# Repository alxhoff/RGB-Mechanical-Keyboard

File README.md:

# RGB-Mechanical-Keyboard

In this repository you will find my PCBs for a mechanical keyboard based around cherry switches and WS2812 single-wire serial RGB LEDs.
The keyboard is broken into two parts, the main keyboard PCB that houses the LEDS, power supply and switches, and a daughterboard that connects via ribbon cable where the controlling microcontroller is mounter.

The keyboard PCB in the latest generation has been been built such that the bottom row can be arranged in many different ways, allowing for unique configuration.
On the to-do list is to add this sort of customizability to more of the keyboard, eg. replacing capslock (totally useless) with a couple of macro keys.

# TODO for V2.1

- [x] Make second-from-bottom row more customizable
- [x] Add a usb 2.0 hub and a couple of usb-c ports to the keyboard.
- [X] Add jumpers to configure rgb rows, for example, daisy chaining multiple rows to reduce required pin count
- [ ] STM32F411 "Blackpill" control board
- [X] Add port for connecting a joystick for mouse functionality
- [X] Add switch for toggling 'BOOT' protocol, ie. device can recognize that it should send 8 byte BOOT compatible HID reports
- [X] Update existing control boards to handle 30 pin ribbon cable
- [X] Add hotswappable sockets
- [X] Make mounting holes elongated to allow for less precision during case fabrication

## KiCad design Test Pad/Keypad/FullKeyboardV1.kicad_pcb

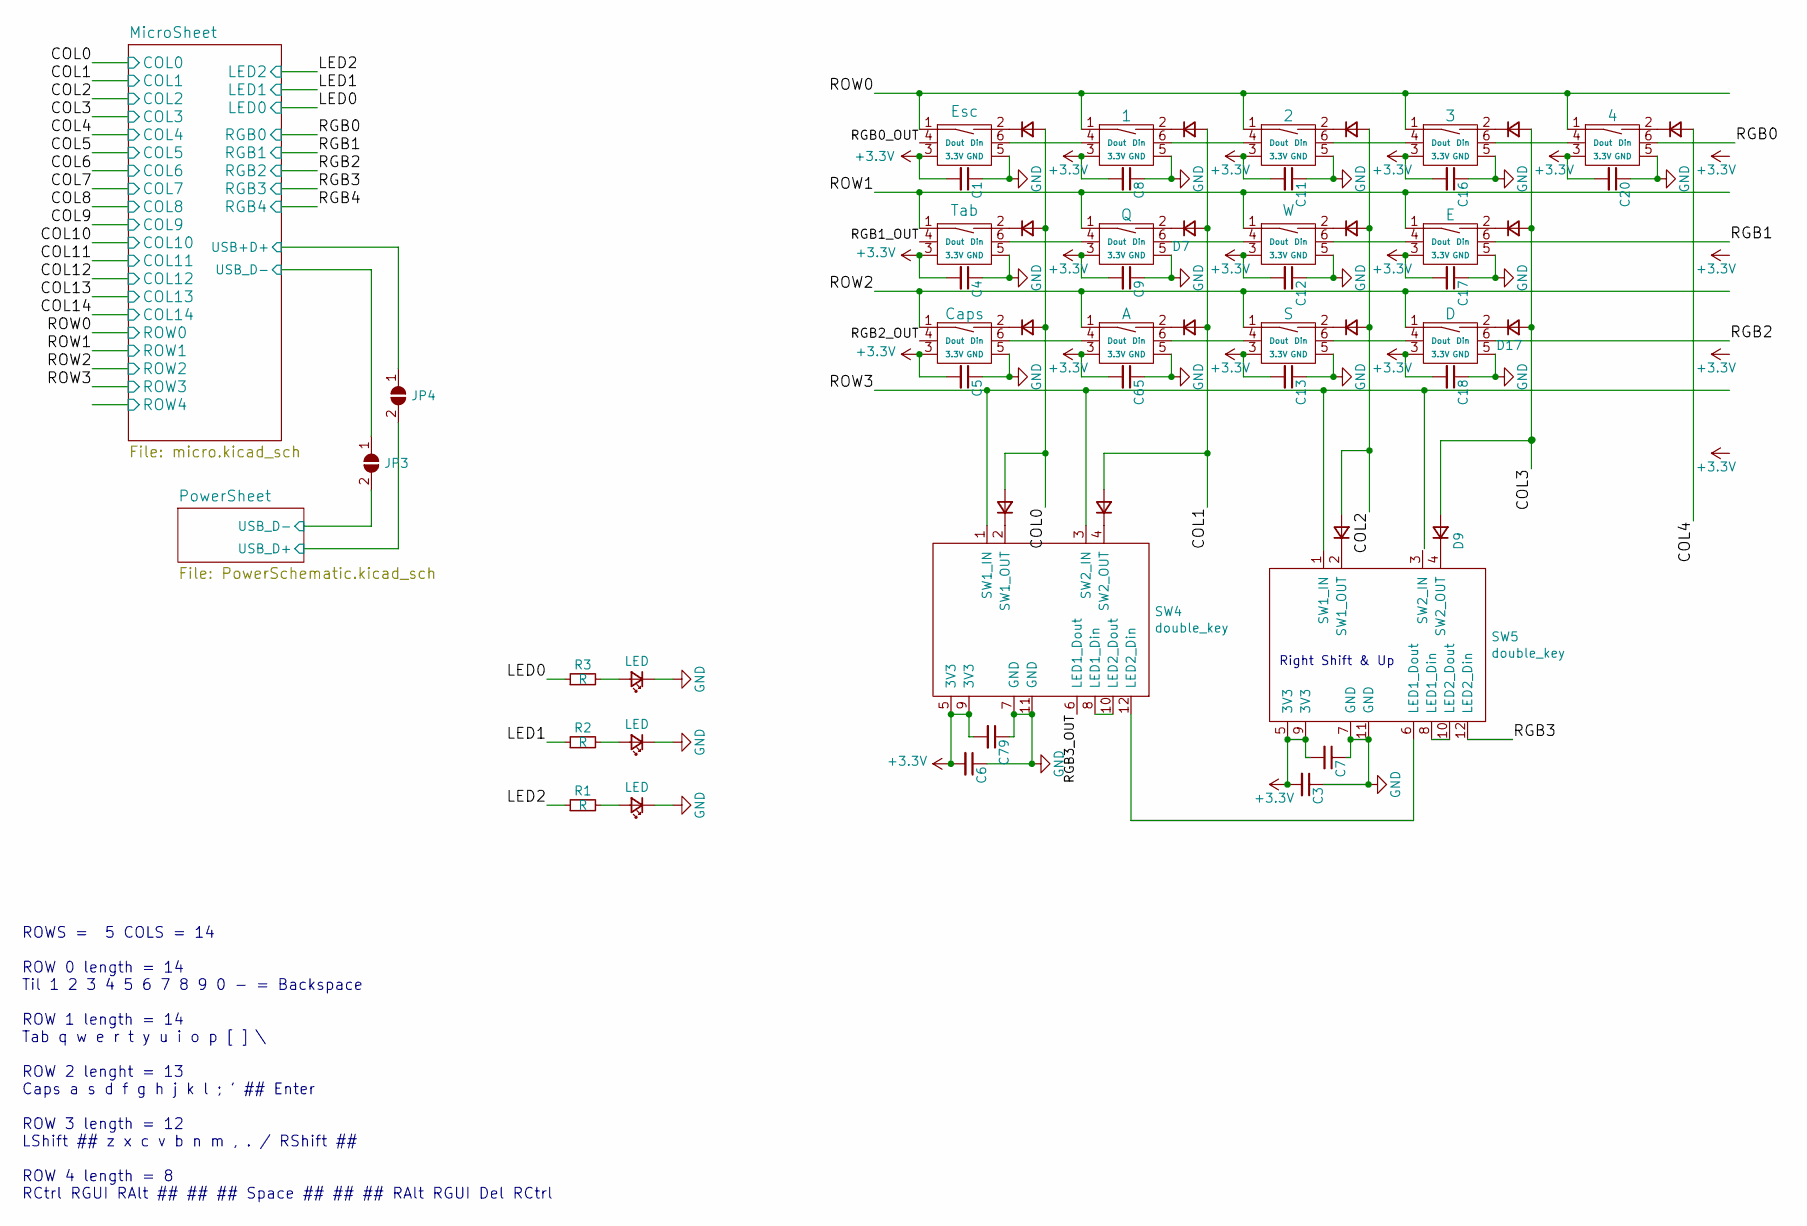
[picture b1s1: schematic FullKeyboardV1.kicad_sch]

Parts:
C1, C3, C4, C5, C6, C7, C8, C9, C11, C12, C13, C16, C17, C18, C20, C65, C79: C_Small; C_0603_1608Metric
D1, D2, D3, D4, D5, D6, D7, D8, D9, D10, D11, D12, D15, D16, D17, D19, D77: D_Small; D_SOD-123
D70, D71, D72: LED; LED_0603_1608Metric
JP3, JP4: SolderJumper_2_Open; SolderJumper-2_P1.3mm_Open_RoundedPad1.0x1.5mm
R1, R2, R3: R; R_0603_1608Metric
SW1: Esc; RGB_CHERRY_PCB_100H_HOTSWAP
SW2: Tab; RGB_CHERRY_PCB_150H_HOTSWAP
SW3: Caps; RGB_CHERRY_PCB_175H_HOTSWAP
SW4: double_key; RGB_CHERRY_SHIFT_ROW_LEFT
SW5: double_key; RGB_CHERRY_SHIFT_RIGHT_2.0
SW6: 1; RGB_CHERRY_PCB_100H_HOTSWAP
SW7: Q; RGB_CHERRY_PCB_100H_HOTSWAP
SW8: A; RGB_CHERRY_PCB_100H_HOTSWAP
SW10: 2; RGB_CHERRY_PCB_100H_HOTSWAP
SW11: W; RGB_CHERRY_PCB_100H_HOTSWAP
SW12: S; RGB_CHERRY_PCB_100H_HOTSWAP
SW15: 3; RGB_CHERRY_PCB_100H_HOTSWAP
SW16: E; RGB_CHERRY_PCB_100H_HOTSWAP
SW17: D; RGB_CHERRY_PCB_100H_HOTSWAP
SW19: 4; RGB_CHERRY_PCB_100H_HOTSWAP

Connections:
/COL0: D1.2 (A), D2.2 (A), D3.2 (A), D4.2 (A); also elsewhere on the board
/COL1: D6.2 (A), D7.2 (A), D8.2 (A), D77.2 (A); also elsewhere on the board
/COL2: D5.2 (A), D10.2 (A), D11.2 (A), D12.2 (A); also elsewhere on the board
/COL3: D9.2 (A), D15.2 (A), D16.2 (A), D17.2 (A); also elsewhere on the board
/COL4: D19.2 (A); also elsewhere on the board
/LED0: R3.1; also elsewhere on the board
/LED1: R2.1; also elsewhere on the board
/LED2: R1.1; also elsewhere on the board
/MicroSheet/USB+D+: JP4.1 (A); also elsewhere on the board
/MicroSheet/USB_D-: JP3.1 (A); also elsewhere on the board
/PowerSheet/USB_D+: JP4.2 (B); also elsewhere on the board
/PowerSheet/USB_D-: JP3.2 (B); also elsewhere on the board
/RGB0: SW19.6 (Din); also elsewhere on the board
/RGB0_OUT: SW1.4 (Dout)
/RGB1: SW16.6 (Din); also elsewhere on the board
/RGB1_OUT: SW2.4 (Dout)
/RGB2: SW17.6 (Din); also elsewhere on the board
/RGB2_OUT: SW3.4 (Dout)
/RGB3: SW5.12 (LED2_Din); also elsewhere on the board
/RGB3_OUT: SW4.6 (LED1_Dout)
/ROW0: SW1.1, SW6.1, SW10.1, SW15.1, SW19.1; also elsewhere on the board
/ROW1: SW2.1, SW7.1, SW11.1, SW16.1; also elsewhere on the board
/ROW2: SW3.1, SW8.1, SW12.1, SW17.1; also elsewhere on the board
/ROW3: SW4.1 (SW1_IN), SW4.3 (SW2_IN), SW5.1 (SW1_IN); also elsewhere on the board
GND: C1.1, C3.1, C4.1, C5.1, C6.1, C7.1, C8.1, C9.1, C11.1, C12.1, C13.1, C16.1, C17.1, C18.1, C20.1, C65.1, C79.1, D70.1 (K), D71.1 (K), D72.1 (K), SW1.5 (GND), SW2.5 (GND), SW3.5 (GND), SW4.7 (GND), SW4.11 (GND), SW5.7 (GND), SW5.11 (GND), SW6.5 (GND), SW7.5 (GND), SW8.5 (GND), SW10.5 (GND), SW11.5 (GND), SW12.5 (GND), SW15.5 (GND), SW16.5 (GND), SW17.5 (GND), SW19.5 (GND); also elsewhere on the board
unnamed: D1.1 (K), SW1.2
unnamed: D2.1 (K), SW2.2
unnamed: D3.1 (K), SW3.2
unnamed: D4.1 (K), SW4.2 (SW1_OUT)
unnamed: D5.1 (K), SW5.2 (SW1_OUT)
unnamed: D6.1 (K), SW6.2
unnamed: D7.1 (K), SW7.2
unnamed: D8.1 (K), SW8.2
unnamed: D9.1 (K), SW5.4 (SW2_OUT)
unnamed: D10.1 (K), SW10.2
unnamed: D11.1 (K), SW11.2
unnamed: D12.1 (K), SW12.2
unnamed: D15.1 (K), SW15.2
unnamed: D16.1 (K), SW16.2
unnamed: D17.1 (K), SW17.2
unnamed: D19.1 (K), SW19.2
unnamed: D70.2 (A), R1.2
unnamed: D71.2 (A), R2.2
unnamed: D72.2 (A), R3.2
unnamed: D77.1 (K), SW4.4 (SW2_OUT)
unnamed: SW1.6 (Din), SW6.4 (Dout)
unnamed: SW2.6 (Din), SW7.4 (Dout)
unnamed: SW3.6 (Din), SW8.4 (Dout)
unnamed: SW4.8 (LED1_Din), SW4.10 (LED2_Dout)
unnamed: SW4.12 (LED2_Din), SW5.6 (LED1_Dout)
unnamed: SW5.8 (LED1_Din), SW5.10 (LED2_Dout)
unnamed: SW6.6 (Din), SW10.4 (Dout)
unnamed: SW10.6 (Din), SW15.4 (Dout)
unnamed: SW7.6 (Din), SW11.4 (Dout)
unnamed: SW11.6 (Din), SW16.4 (Dout)
unnamed: SW8.6 (Din), SW12.4 (Dout)
unnamed: SW12.6 (Din), SW17.4 (Dout)
unnamed: SW15.6 (Din), SW19.4 (Dout)

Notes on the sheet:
Right Shift & Up
ROWS = 5 COLS = 14 ROW 0 length = 14 Til 1 2 3 4 5 6 7 8 9 0 - = Backspace ROW 1 length = 14 Tab q w e r t y u i o p [ ] \ ROW 2 lenght = 13 Caps a s d f g h j k l ; ' ## Enter ROW 3 length = 12 LShift ## z x c v b n m , . / RShift ## ROW 4 length = 8 RCtrl RGUI RAlt ## ## ## Space ## ## ## RAlt RG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

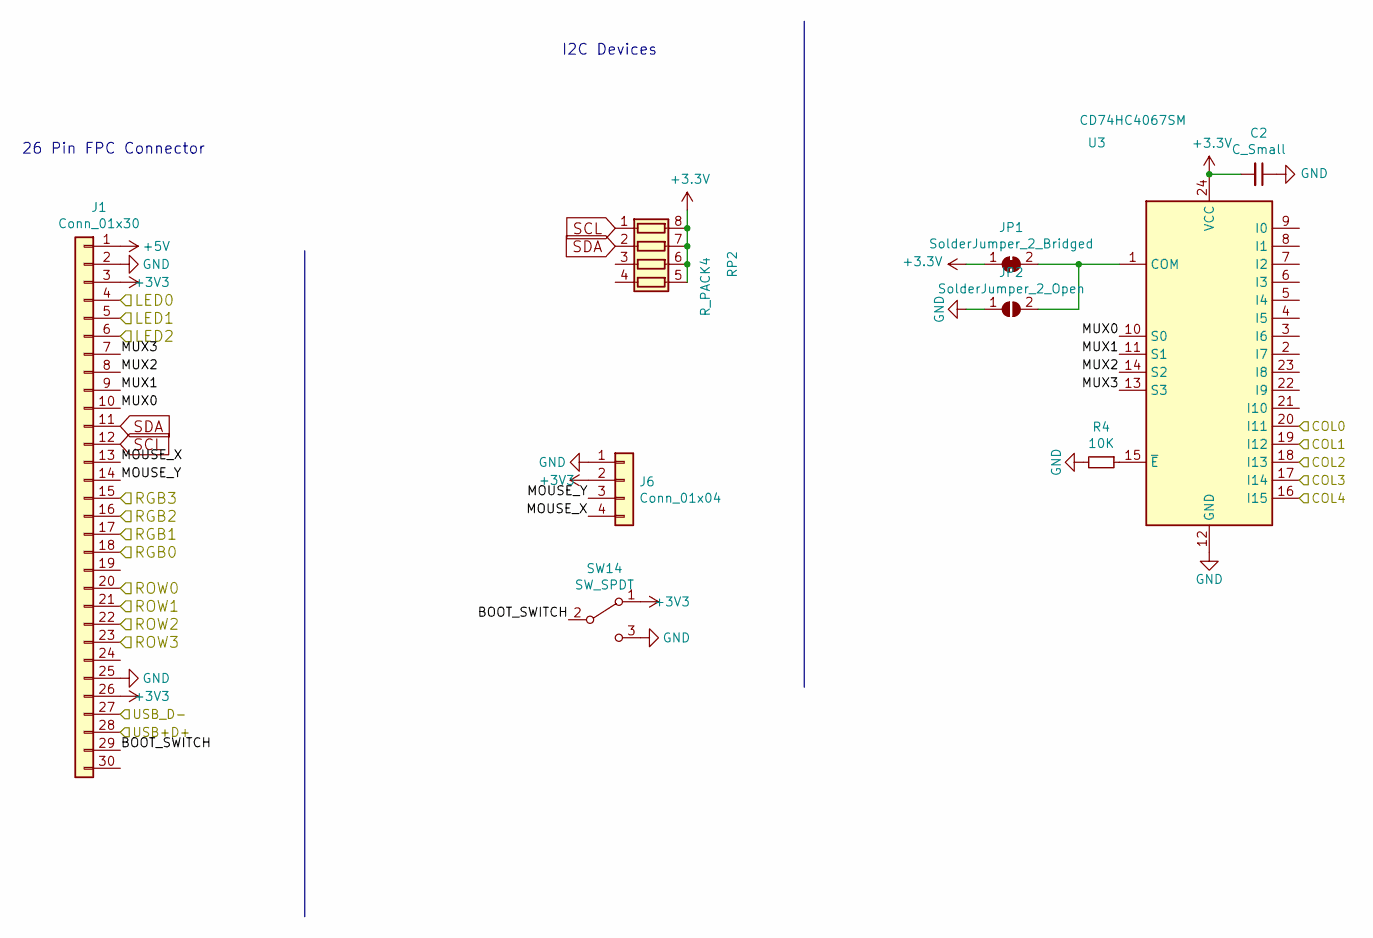
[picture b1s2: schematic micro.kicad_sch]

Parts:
C2: C_Small; C_0603_1608Metric
J1: Conn_01x30; Hirose_FH12-30S-0.5SH_1x30-1MP_P0.50mm_Horizontal
J6: Conn_01x04; JST_PH_S4B-PH-SM4-TB_1x04-1MP_P2.00mm_Horizontal
JP1: SolderJumper_2_Bridged; SolderJumper-2_P1.3mm_Bridged_RoundedPad1.0x1.5mm
JP2: SolderJumper_2_Open; SolderJumper-2_P1.3mm_Open_RoundedPad1.0x1.5mm
R4: 10K; R_0603_1608Metric
RP2: R_PACK4; R_Array_Concave_4x0402
SW14: SW_SPDT; SS12F23
U3: CD74HC4067SM; SSOP-24_5.3x8.2mm_P0.65mm

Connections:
+5V: J1.1; also elsewhere on the board
/COL0: U3.20 (I11); also elsewhere on the board
/COL1: U3.19 (I12); also elsewhere on the board
/COL2: U3.18 (I13); also elsewhere on the board
/COL3: U3.17 (I14); also elsewhere on the board
/COL4: U3.16 (I15); also elsewhere on the board
/LED0: J1.4; also elsewhere on the board
/LED1: J1.5; also elsewhere on the board
/LED2: J1.6; also elsewhere on the board
/MicroSheet/BOOT_SWITCH: J1.29, SW14.2 (B)
/MicroSheet/MOUSE_X: J1.13, J6.4
/MicroSheet/MOUSE_Y: J1.14, J6.3
/MicroSheet/MUX0: J1.10, U3.10 (S0)
/MicroSheet/MUX1: J1.9, U3.11 (S1)
/MicroSheet/MUX2: J1.8, U3.14 (S2)
/MicroSheet/MUX3: J1.7, U3.13 (S3)
/MicroSheet/USB+D+: J1.28; also elsewhere on the board
/MicroSheet/USB_D-: J1.27; also elsewhere on the board
/RGB0: J1.18; also elsewhere on the board
/RGB1: J1.17; also elsewhere on the board
/RGB2: J1.16; also elsewhere on the board
/RGB3: J1.15; also elsewhere on the board
/ROW0: J1.20; also elsewhere on the board
/ROW1: J1.21; also elsewhere on the board
/ROW2: J1.22; also elsewhere on the board
/ROW3: J1.23; also elsewhere on the board
GND: C2.1, J1.2, J1.25, J6.1, JP2.1 (A), R4.2, SW14.3 (C), U3.12 (GND); also elsewhere on the board
unnamed: JP1.2 (B), JP2.2 (B), U3.1 (COM)
unnamed: R4.1, U3.15 (~E)
SCL: J1.12, RP2.1 (R1.1)
SDA: J1.11, RP2.2 (R2.1)

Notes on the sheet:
I2C Devices
26 Pin FPC Connector

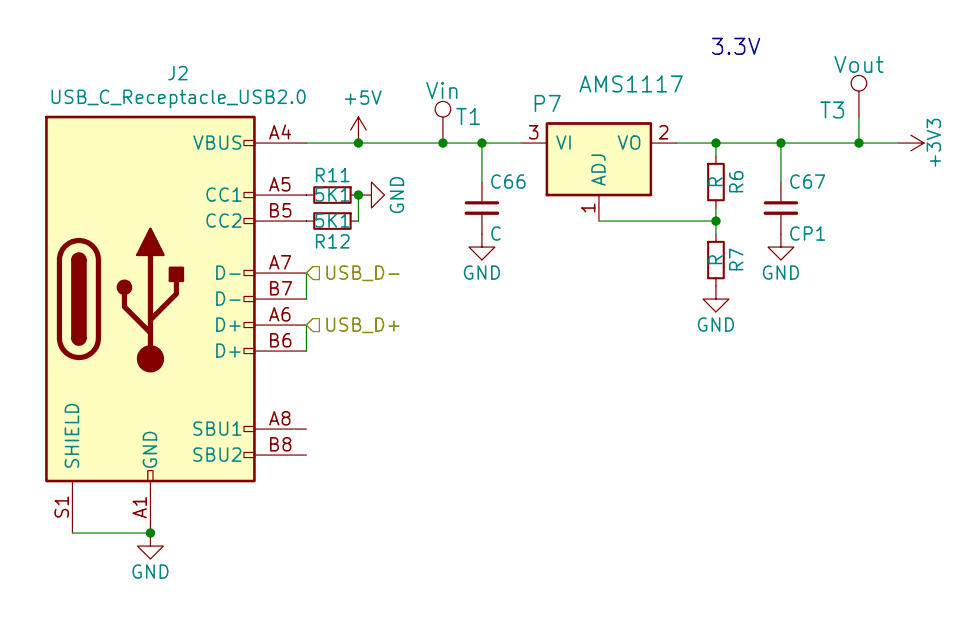
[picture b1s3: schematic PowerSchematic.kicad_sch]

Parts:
C66: C; C_0603_1608Metric
C67: CP1; C_0603_1608Metric
J2: USB_C_Receptacle_USB2.0; USB_C_Receptacle_HRO_TYPE-C-31-M-12
P7: AMS1117; SOT-223
R6, R7: R; R_0603_1608Metric
R11, R12: 5K1; R_0603_1608Metric
T1: Vin; TestPoint_Pad_1.0x1.0mm
T3: Vout; TestPoint_Pad_1.0x1.0mm

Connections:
+5V: C66.1, J2.A4 (VBUS), J2.A9 (VBUS), J2.B4 (VBUS), J2.B9 (VBUS), P7.3 (VI), T1.1; also elsewhere on the board
/PowerSheet/USB_D+: J2.A6 (D+), J2.B6 (D+); also elsewhere on the board
/PowerSheet/USB_D-: J2.A7 (D-), J2.B7 (D-); also elsewhere on the board
GND: C66.2, C67.2, J2.A1 (GND), J2.A12 (GND), J2.B1 (GND), J2.B12 (GND), J2.S1 (SHIELD), R7.2, R11.1, R12.1; also elsewhere on the board
unnamed: J2.A5 (CC1), R11.2
unnamed: J2.B5 (CC2), R12.2
unnamed: P7.1 (ADJ), R6.2, R7.1

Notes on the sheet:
3.3V

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
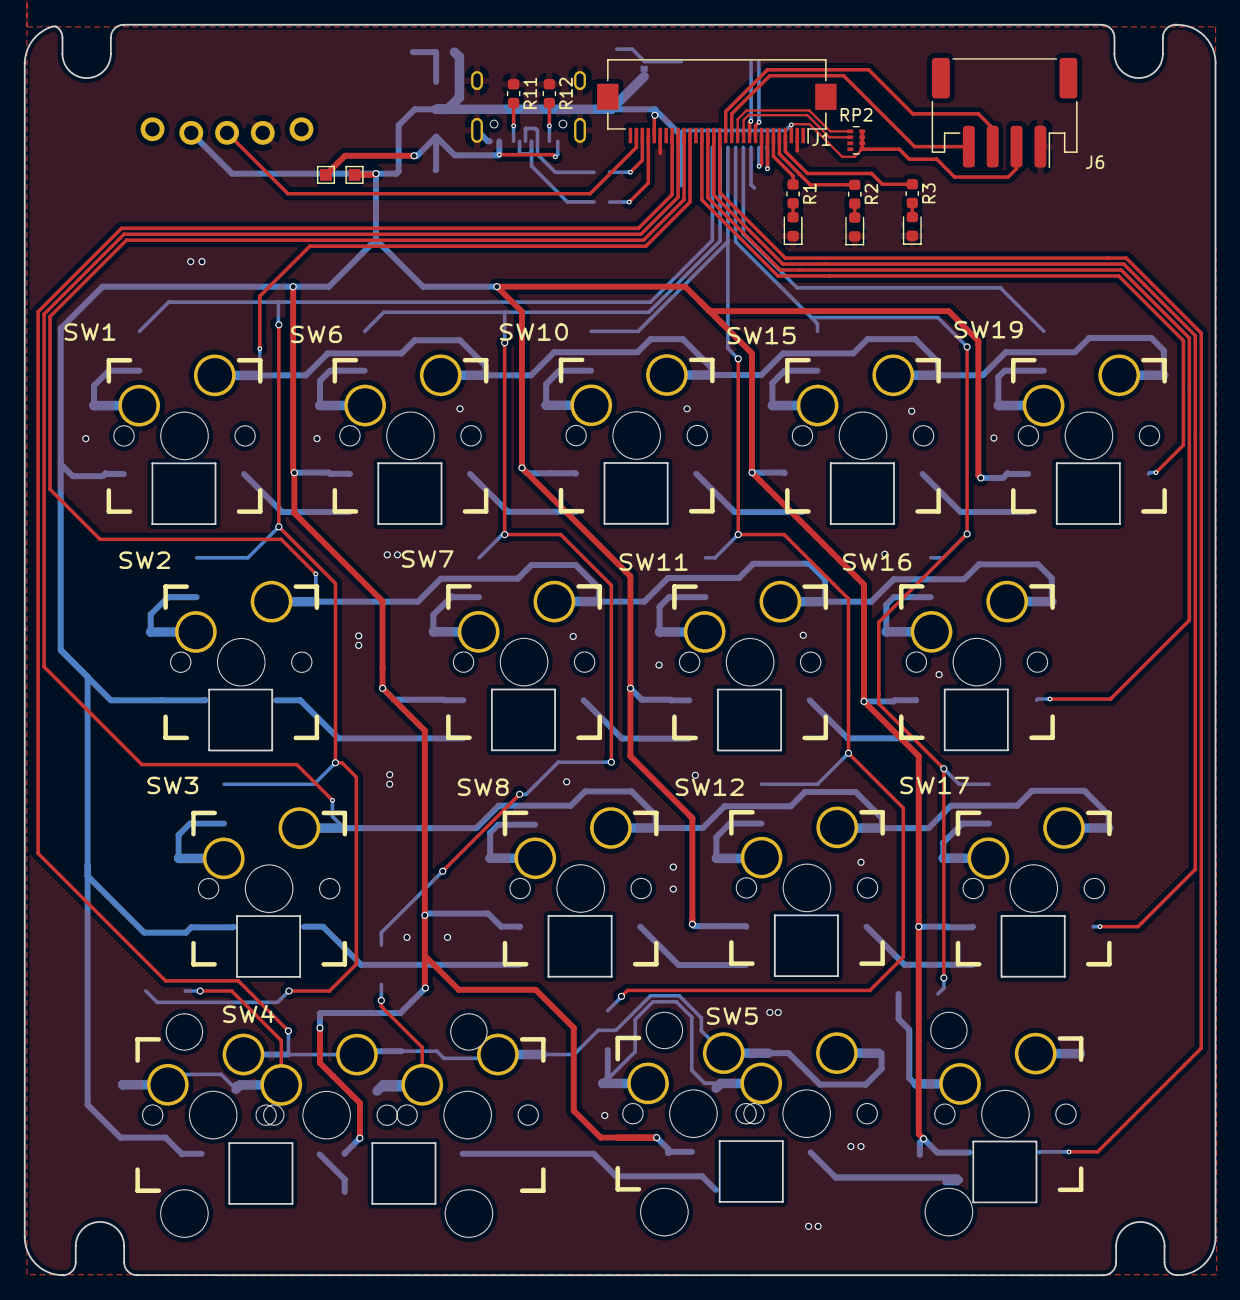
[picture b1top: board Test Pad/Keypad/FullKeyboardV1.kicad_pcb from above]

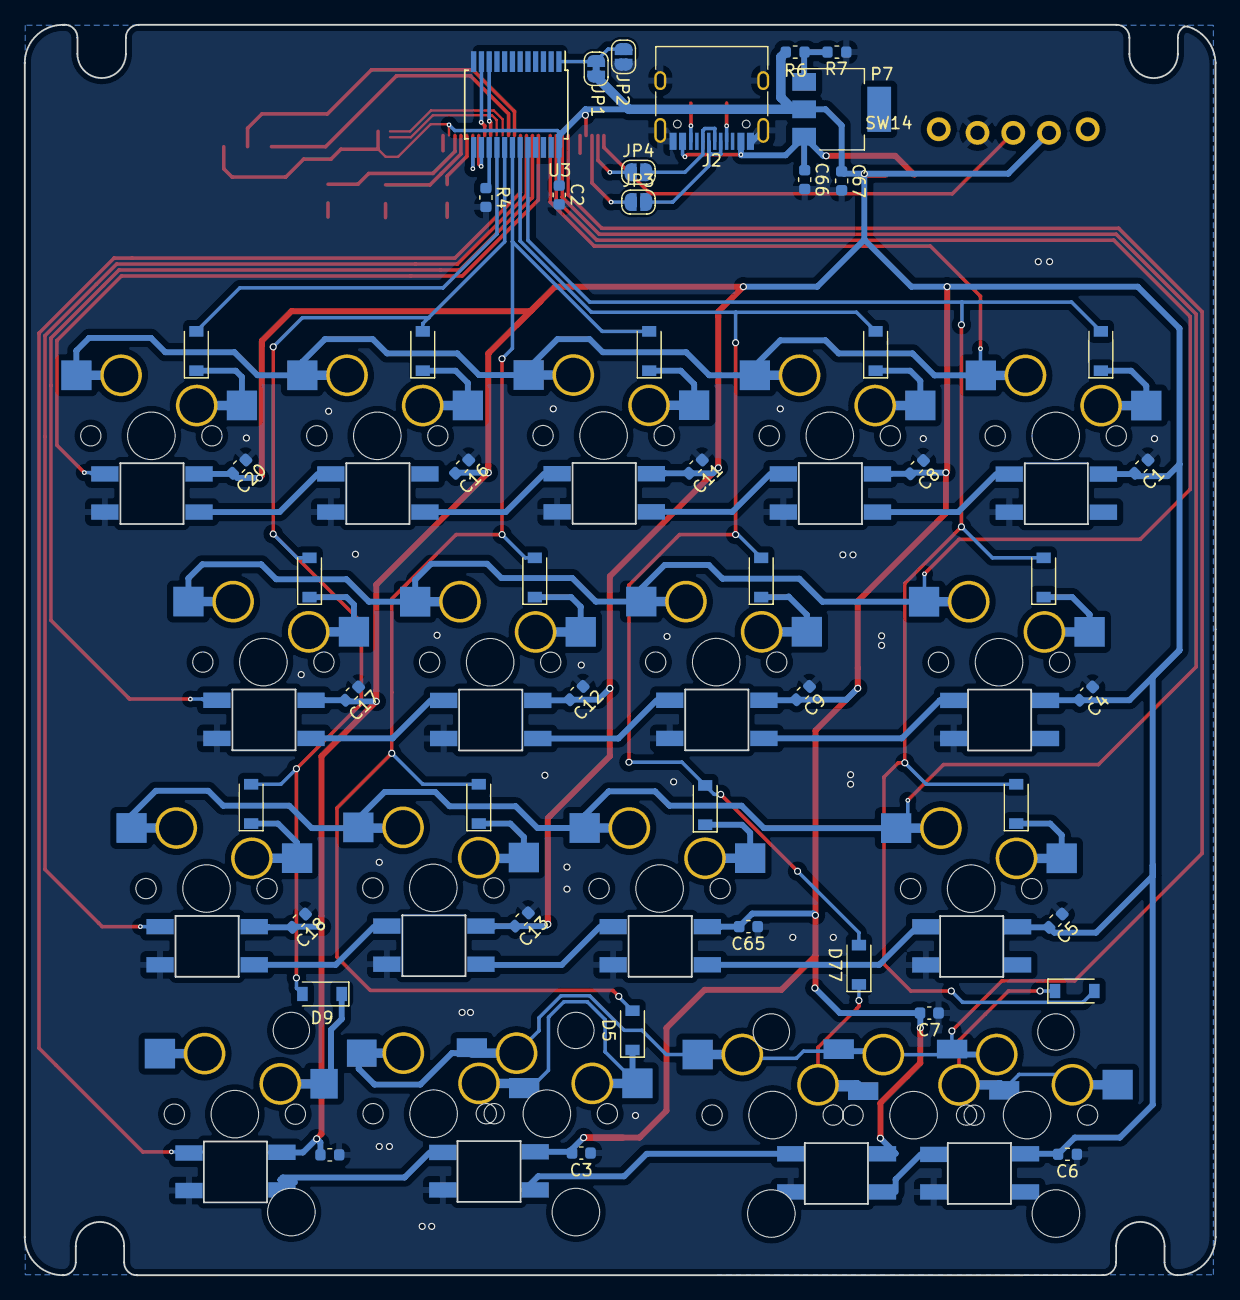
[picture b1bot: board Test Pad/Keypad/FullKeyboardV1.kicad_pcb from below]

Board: 2 copper layers, 99.9 x 104.9 mm, 76 parts (48 on the bottom side), 70 nets.

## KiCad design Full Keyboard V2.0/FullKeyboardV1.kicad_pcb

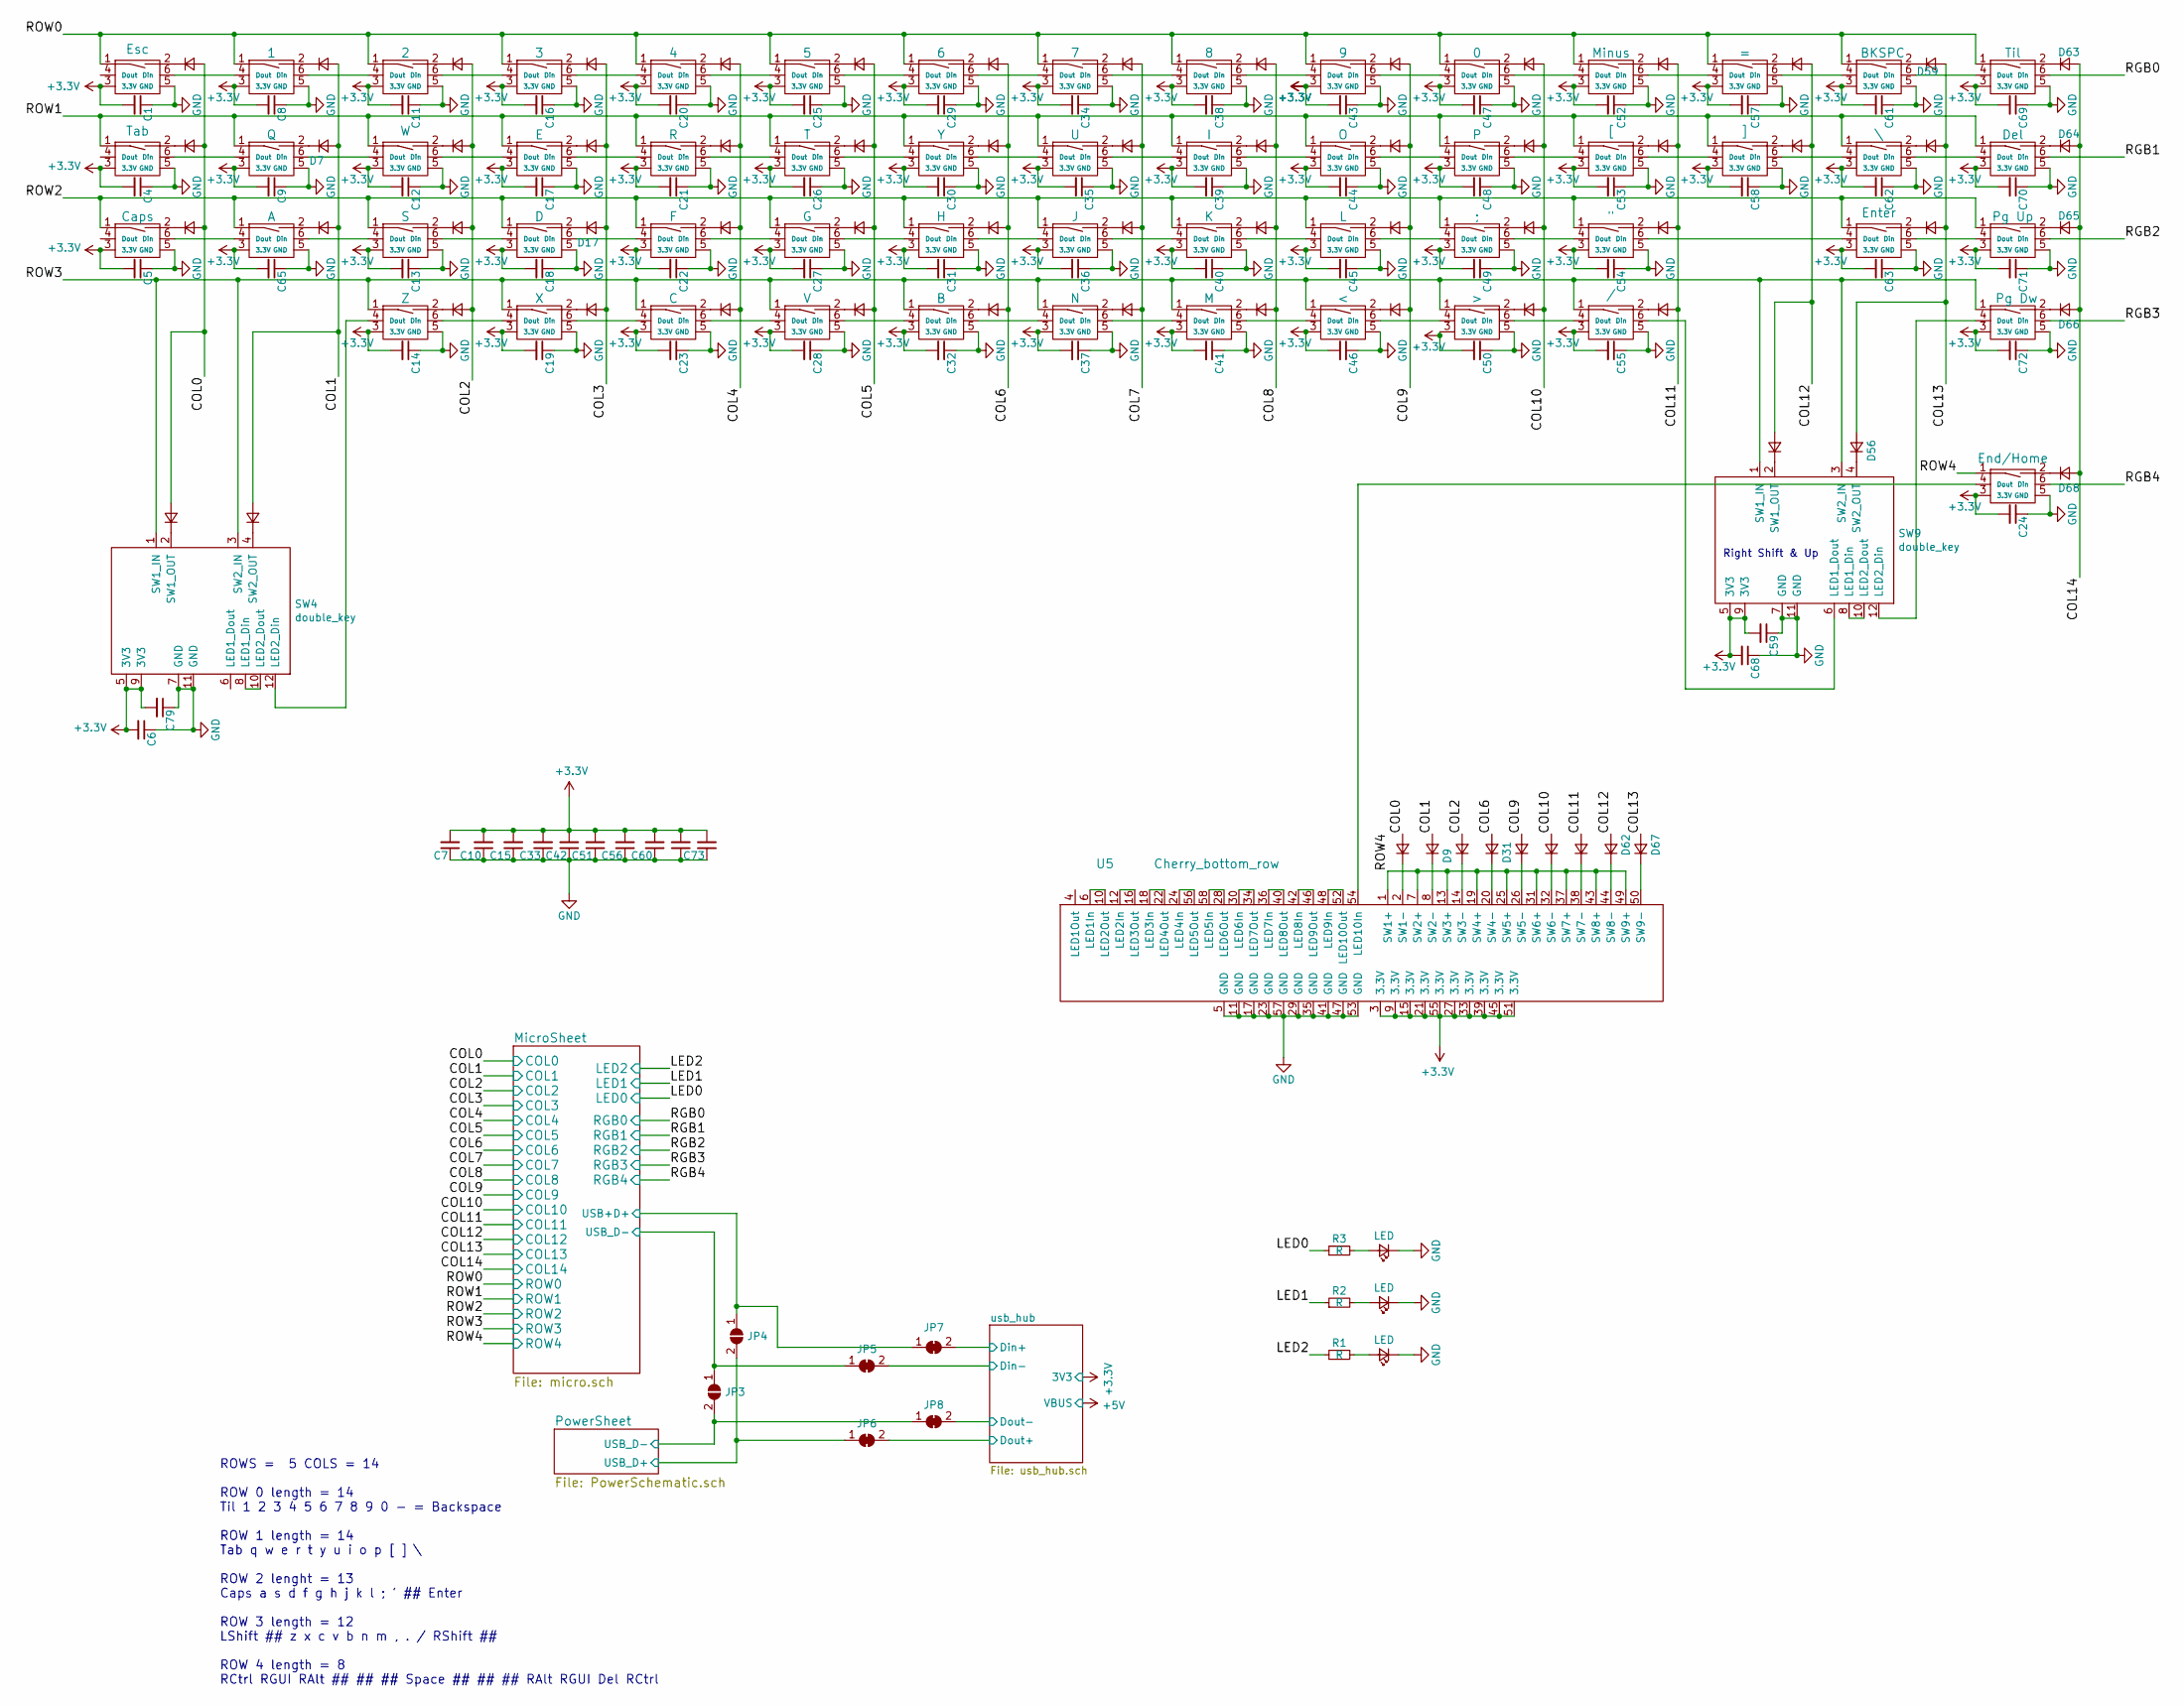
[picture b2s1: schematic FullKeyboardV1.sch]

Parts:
C1, C4, C5, C6, C7, C8, C9, C10, C11, C12, C13, C14, C15, C16, C17, C18, C19, C20, C21, C22, C23, C24, C25, C26, C27, C28, C29, C30, C31, C32, C33, C34, C35, C36, C37, C38, C39, C40, C41, C42, C43, C44, C45, C46, C47, C48, C49, C50, C51, C52, C53, C54, C55, C56, C57, C58, C59, C60, C61, C62, C63, C64, C65, C68, C69, C70, C71, C72, C73, C79: C_Small; C_0603_1608Metric
D1, D2, D3, D4, D5, D6, D7, D8, D9, D10, D11, D12, D13, D14, D15, D16, D17, D18, D19, D20, D21, D22, D23, D24, D25, D26, D27, D28, D29, D30, D31, D32, D33, D34, D35, D36, D37, D38, D39, D40, D41, D42, D43, D44, D45, D46, D47, D48, D49, D50, D51, D52, D53, D54, D55, D56, D57, D58, D59, D60, D61, D62, D63, D64, D65, D66, D67, D68, D77: D_Small; D_SOD-123
D70, D71, D72: LED; LED_0603_1608Metric
JP3, JP4: SolderJumper_2_Open; SolderJumper-2_P1.3mm_Open_RoundedPad1.0x1.5mm
JP5, JP6, JP7, JP8: SolderJumper_2_Bridged; SolderJumper-2_P1.3mm_Bridged_RoundedPad1.0x1.5mm
R1, R2, R3: R; R_0603_1608Metric
SW1: Esc; RGB_CHERRY_PCB_100H
SW2: Tab; RGB_CHERRY_PCB_150H
SW3: Caps; RGB_CHERRY_PCB_175H
SW4: double_key; RGB_CHERRY_SHIFT_ROW_LEFT
SW5: End/Home; RGB_CHERRY_PCB_100H
SW6: 1; RGB_CHERRY_PCB_100H
SW7: Q; RGB_CHERRY_PCB_100H
SW8: A; RGB_CHERRY_PCB_100H
SW9: double_key; RGB_CHERRY_SHIFT_RIGHT_2.0
SW10: 2; RGB_CHERRY_PCB_100H
SW11: W; RGB_CHERRY_PCB_100H
SW12: S; RGB_CHERRY_PCB_100H
SW13: Z; RGB_CHERRY_PCB_100H
SW15: 3; RGB_CHERRY_PCB_100H
SW16: E; RGB_CHERRY_PCB_100H
SW17: D; RGB_CHERRY_PCB_100H
SW18: X; RGB_CHERRY_PCB_100H
SW19: 4; RGB_CHERRY_PCB_100H
SW20: R; RGB_CHERRY_PCB_100H
SW21: F; RGB_CHERRY_PCB_100H
SW22: C; RGB_CHERRY_PCB_100H
SW23: 5; RGB_CHERRY_PCB_100H
SW24: T; RGB_CHERRY_PCB_100H
SW25: G; RGB_CHERRY_PCB_100H
SW26: V; RGB_CHERRY_PCB_100H
SW27: 6; RGB_CHERRY_PCB_100H
SW28: Y; RGB_CHERRY_PCB_100H
SW29: H; RGB_CHERRY_PCB_100H
SW30: B; RGB_CHERRY_PCB_100H
SW32: 7; RGB_CHERRY_PCB_100H
SW33: U; RGB_CHERRY_PCB_100H
SW34: J; RGB_CHERRY_PCB_100H
SW35: N; RGB_CHERRY_PCB_100H
SW36: 8; RGB_CHERRY_PCB_100H
SW37: I; RGB_CHERRY_PCB_100H
SW38: K; RGB_CHERRY_PCB_100H
SW39: M; RGB_CHERRY_PCB_100H
SW40: 9; RGB_CHERRY_PCB_100H
SW41: O; RGB_CHERRY_PCB_100H
SW42: L; RGB_CHERRY_PCB_100H
SW43: <; RGB_CHERRY_PCB_100H
SW44: 0; RGB_CHERRY_PCB_100H
SW45: P; RGB_CHERRY_PCB_100H
SW46: ;; RGB_CHERRY_PCB_100H
SW47: >; RGB_CHERRY_PCB_100H
SW49: Minus; RGB_CHERRY_PCB_100H
SW50: [; RGB_CHERRY_PCB_100H
SW51: \"; RGB_CHERRY_PCB_100H
SW52: /; RGB_CHERRY_PCB_100H
SW54: =; RGB_CHERRY_PCB_100H
SW55: ]; RGB_CHERRY_PCB_100H
SW59: BKSPC; RGB_CHERRY_PCB_200H
SW60: \\; RGB_CHERRY_PCB_150H
SW61: Enter; RGB_CHERRY_PCB_225H
SW63: Til; RGB_CHERRY_PCB_100H
SW64: Del; RGB_CHERRY_PCB_100H
SW65: Pg Up; RGB_CHERRY_PCB_100H
SW66: Pg Dw; RGB_CHERRY_PCB_100H
U5: Cherry_bottom_row; RGB_CHERRY_SPACEBAR_ROW

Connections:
/COL0: D1.2 (A), D2.2 (A), D3.2 (A), D4.2 (A), D5.2 (A); also elsewhere on the board
/COL1: D6.2 (A), D7.2 (A), D8.2 (A), D9.2 (A), D77.2 (A); also elsewhere on the board
/COL2: D10.2 (A), D11.2 (A), D12.2 (A), D13.2 (A), D14.2 (A); also elsewhere on the board
/COL3: D15.2 (A), D16.2 (A), D17.2 (A), D18.2 (A); also elsewhere on the board
/COL4: D19.2 (A), D20.2 (A), D21.2 (A), D22.2 (A); also elsewhere on the board
/COL5: D23.2 (A), D24.2 (A), D25.2 (A), D26.2 (A); also elsewhere on the board
/COL6: D27.2 (A), D28.2 (A), D29.2 (A), D30.2 (A), D31.2 (A); also elsewhere on the board
/COL7: D32.2 (A), D33.2 (A), D34.2 (A), D35.2 (A); also elsewhere on the board
/COL8: D36.2 (A), D37.2 (A), D38.2 (A), D39.2 (A); also elsewhere on the board
/COL9: D40.2 (A), D41.2 (A), D42.2 (A), D43.2 (A), D48.2 (A); also elsewhere on the board
/COL10: D44.2 (A), D45.2 (A), D46.2 (A), D47.2 (A), D53.2 (A); also elsewhere on the board
/COL11: D49.2 (A), D50.2 (A), D51.2 (A), D52.2 (A), D58.2 (A); also elsewhere on the board
/COL12: D54.2 (A), D55.2 (A), D57.2 (A), D62.2 (A); also elsewhere on the board
/COL13: D56.2 (A), D59.2 (A), D60.2 (A), D61.2 (A), D67.2 (A); also elsewhere on the board
/COL14: D63.2 (A), D64.2 (A), D65.2 (A), D66.2 (A), D68.2 (A); also elsewhere on the board
/LED0: R3.1; also elsewhere on the board
/LED1: R2.1; also elsewhere on the board
/LED2: R1.1; also elsewhere on the board
/MicroSheet/USB+D+: JP4.1 (A), JP7.1 (A); also elsewhere on the board
/MicroSheet/USB_D-: JP3.1 (A), JP5.1 (A); also elsewhere on the board
/PowerSheet/USB_D+: JP4.2 (B), JP6.1 (A); also elsewhere on the board
/PowerSheet/USB_D-: JP3.2 (B), JP8.1 (A); also elsewhere on the board
/RGB0: SW63.6 (Din); also elsewhere on the board
/RGB0_OUT: SW1.4 (Dout); also elsewhere on the board
/RGB1: SW64.6 (Din); also elsewhere on the board
/RGB1_OUT: SW2.4 (Dout); also elsewhere on the board
/RGB2: SW65.6 (Din); also elsewhere on the board
/RGB2_OUT: SW3.4 (Dout); also elsewhere on the board
/RGB3: SW66.6 (Din); also elsewhere on the board
/RGB3_OUT: SW4.6 (LED1_Dout); also elsewhere on the board
/RGB4: SW5.6 (Din); also elsewhere on the board
/RGB4_OUT: U5.4 (LED1Out)
/ROW0: SW1.1, SW6.1, SW10.1, SW15.1, SW19.1, SW23.1, SW27.1, SW32.1, SW36.1, SW40.1, SW44.1, SW49.1, SW54.1, SW59.1, SW63.1; also elsewhere on the board
/ROW1: SW2.1, SW7.1, SW11.1, SW16.1, SW20.1, SW24.1, SW28.1, SW33.1, SW37.1, SW41.1, SW45.1, SW50.1, SW55.1, SW60.1, SW64.1; also elsewhere on the board
/ROW2: SW3.1, SW8.1, SW12.1, SW17.1, SW21.1, SW25.1, SW29.1, SW34.1, SW38.1, SW42.1, SW46.1, SW51.1, SW61.1, SW65.1; also elsewhere on the board
/ROW3: SW4.1 (SW1_IN), SW4.3 (SW2_IN), SW9.1 (SW1_IN), SW9.3 (SW2_IN), SW13.1, SW18.1, SW22.1, SW26.1, SW30.1, SW35.1, SW39.1, SW43.1, SW47.1, SW52.1, SW66.1; also elsewhere on the board
/ROW4: SW5.1, U5.1 (SW1+), U5.7 (SW2+), U5.13 (SW3+), U5.19 (SW4+), U5.25 (SW5+), U5.31 (SW6+), U5.37 (SW7+), U5.43 (SW8+), U5.49 (SW9+); also elsewhere on the board
/usb_hub/Din+: JP7.2 (B); also elsewhere on the board
/usb_hub/Din-: JP5.2 (B); also elsewhere on the board
/usb_hub/Dout+: JP6.2 (B); also elsewhere on the board
/usb_hub/Dout-: JP8.2 (B); also elsewhere on the board
GND: C1.1, C4.1, C5.1, C6.1, C7.1, C8.1, C9.1, C10.1, C11.1, C12.1, C13.1, C14.1, C15.1, C16.1, C17.1, C18.1, C19.1, C20.1, C21.1, C22.1, C23.1, C24.1, C25.1, C26.1, C27.1, C28.1, C29.1, C30.1, C31.1, C32.1, C33.1, C34.1, C35.1, C36.1, C37.1, C38.1, C39.1, C40.1, C41.1, C42.1, C43.1, C44.1, C45.1, C46.1, C47.1, C48.1, C49.1, C50.1, C51.1, C52.1, C53.1, C54.1, C55.1, C56.1, C57.1, C58.1, C59.1, C60.1, C61.1, C62.1, C63.1, C64.1, C65.1, C68.1, C69.1, C70.1, C71.1, C72.1, C73.1, C79.1, D70.1 (K), D71.1 (K), D72.1 (K), SW1.5 (GND), SW2.5 (GND), SW3.5 (GND), SW4.7 (GND), SW4.11 (GND), SW5.5 (GND), SW6.5 (GND), SW7.5 (GND), SW8.5 (GND), SW9.7 (GND), SW9.11 (GND), SW10.5 (GND), SW11.5 (GND), SW12.5 (GND), SW13.5 (GND), SW15.5 (GND), SW16.5 (GND), SW17.5 (GND), SW18.5 (GND), SW19.5 (GND), SW20.5 (GND), SW21.5 (GND), SW22.5 (GND), SW23.5 (GND), SW24.5 (GND), SW25.5 (GND), SW26.5 (GND), SW27.5 (GND), SW28.5 (GND), SW29.5 (GND), SW30.5 (GND), SW32.5 (GND), SW33.5 (GND), SW34.5 (GND), SW35.5 (GND), SW36.5 (GND), SW37.5 (GND), SW38.5 (GND), SW39.5 (GND), SW40.5 (GND), SW41.5 (GND), SW42.5 (GND), SW43.5 (GND), SW44.5 (GND), SW45.5 (GND), SW46.5 (GND), SW47.5 (GND), SW49.5 (GND), SW50.5 (GND), SW51.5 (GND), SW52.5 (GND), SW54.5 (GND), SW55.5 (GND), SW59.5 (GND), SW60.5 (GND), SW61.5 (GND), SW63.5 (GND), SW64.5 (GND), SW65.5 (GND), SW66.5 (GND), U5.5 (GND), U5.11 (GND), U5.17 (GND), U5.23 (GND), U5.29 (GND), U5.35 (GND), U5.41 (GND), U5.47 (GND), U5.53 (GND), U5.57 (GND); also elsewhere on the board
unnamed: D1.1 (K), SW1.2
unnamed: D2.1 (K), SW2.2
unnamed: D3.1 (K), SW3.2
unnamed: D4.1 (K), SW4.2 (SW1_OUT)
unnamed: D5.1 (K), U5.2 (SW1-)
unnamed: D6.1 (K), SW6.2
unnamed: D7.1 (K), SW7.2
unnamed: D8.1 (K), SW8.2
unnamed: D9.1 (K), U5.8 (SW2-)
unnamed: D10.1 (K), SW10.2
unnamed: D11.1 (K), SW11.2
unnamed: D12.1 (K), SW12.2
unnamed: D13.1 (K), SW13.2
unnamed: D14.1 (K), U5.14 (SW3-)
unnamed: D15.1 (K), SW15.2
unnamed: D16.1 (K), SW16.2
unnamed: D17.1 (K), SW17.2
unnamed: D18.1 (K), SW18.2
unnamed: D19.1 (K), SW19.2
unnamed: D20.1 (K), SW20.2
unnamed: D21.1 (K), SW21.2
unnamed: D22.1 (K), SW22.2
unnamed: D23.1 (K), SW23.2
unnamed: D24.1 (K), SW24.2
unnamed: D25.1 (K), SW25.2
unnamed: D26.1 (K), SW26.2
unnamed: D27.1 (K), SW27.2
unnamed: D28.1 (K), SW28.2
unnamed: D29.1 (K), SW29.2
unnamed: D30.1 (K), SW30.2
unnamed: D31.1 (K), U5.20 (SW4-)
unnamed: D32.1 (K), SW32.2
unnamed: D33.1 (K), SW33.2
unnamed: D34.1 (K), SW34.2
unnamed: D35.1 (K), SW35.2
unnamed: D36.1 (K), SW36.2
unnamed: D37.1 (K), SW37.2
unnamed: D38.1 (K), SW38.2
unnamed: D39.1 (K), SW39.2
unnamed: D40.1 (K), SW40.2
unnamed: D41.1 (K), SW41.2
unnamed: D42.1 (K), SW42.2
unnamed: D43.1 (K), SW43.2
unnamed: D44.1 (K), SW44.2
unnamed: D45.1 (K), SW45.2
unnamed: D46.1 (K), SW46.2
unnamed: D47.1 (K), SW47.2
unnamed: D48.1 (K), U5.26 (SW5-)
unnamed: D49.1 (K), SW49.2
unnamed: D50.1 (K), SW50.2
unnamed: D51.1 (K), SW51.2
unnamed: D52.1 (K), SW52.2
unnamed: D53.1 (K), U5.32 (SW6-)
unnamed: D54.1 (K), SW54.2
unnamed: D55.1 (K), SW55.2
unnamed: D56.1 (K), SW9.4 (SW2_OUT)
unnamed: D57.1 (K), SW9.2 (SW1_OUT)
unnamed: D58.1 (K), U5.38 (SW7-)
unnamed: D59.1 (K), SW59.2
unnamed: D60.1 (K), SW60.2
unnamed: D61.1 (K), SW61.2
unnamed: D62.1 (K), U5.44 (SW8-)
unnamed: D63.1 (K), SW63.2
unnamed: D64.1 (K), SW64.2
unnamed: D65.1 (K), SW65.2
unnamed: D66.1 (K), SW66.2
unnamed: D67.1 (K), U5.50 (SW9-)
unnamed: D68.1 (K), SW5.2
unnamed: D70.2 (A), R1.2
unnamed: D71.2 (A), R2.2
unnamed: D72.2 (A), R3.2
unnamed: D77.1 (K), SW4.4 (SW2_OUT)
unnamed: SW1.6 (Din), SW6.4 (Dout)
unnamed: SW2.6 (Din), SW7.4 (Dout)
unnamed: SW3.6 (Din), SW8.4 (Dout)
unnamed: SW4.8 (LED1_Din), SW4.10 (LED2_Dout)
unnamed: SW5.4 (Dout), U5.54 (LED10In)
unnamed: SW9.8 (LED1_Din), SW9.10 (LED2_Dout)
unnamed: SW6.6 (Din), SW10.4 (Dout)
unnamed: SW10.6 (Din), SW15.4 (Dout)
unnamed: SW7.6 (Din), SW11.4 (Dout)
unnamed: SW11.6 (Din), SW16.4 (Dout)
unnamed: SW8.6 (Din), SW12.4 (Dout)
unnamed: SW12.6 (Din), SW17.4 (Dout)
unnamed: SW4.12 (LED2_Din), SW13.4 (Dout)
unnamed: SW13.6 (Din), SW18.4 (Dout)
unnamed: SW15.6 (Din), SW19.4 (Dout)
unnamed: SW16.6 (Din), SW20.4 (Dout)
unnamed: SW17.6 (Din), SW21.4 (Dout)
unnamed: SW18.6 (Din), SW22.4 (Dout)
unnamed: SW19.6 (Din), SW23.4 (Dout)
unnamed: SW20.6 (Din), SW24.4 (Dout)
unnamed: SW21.6 (Din), SW25.4 (Dout)
unnamed: SW22.6 (Din), SW26.4 (Dout)
unnamed: SW23.6 (Din), SW27.4 (Dout)
unnamed: SW24.6 (Din), SW28.4 (Dout)
unnamed: SW25.6 (Din), SW29.4 (Dout)
unnamed: SW26.6 (Din), SW30.4 (Dout)
unnamed: SW27.6 (Din), SW32.4 (Dout)
unnamed: SW28.6 (Din), SW33.4 (Dout)
unnamed: SW29.6 (Din), SW34.4 (Dout)
unnamed: SW30.6 (Din), SW35.4 (Dout)
unnamed: SW32.6 (Din), SW36.4 (Dout)
unnamed: SW33.6 (Din), SW37.4 (Dout)
unnamed: SW34.6 (Din), SW38.4 (Dout)
unnamed: SW35.6 (Din), SW39.4 (Dout)
unnamed: SW36.6 (Din), SW40.4 (Dout)
unnamed: SW37.6 (Din), SW41.4 (Dout)
unnamed: SW38.6 (Din), SW42.4 (Dout)
unnamed: SW39.6 (Din), SW43.4 (Dout)
unnamed: SW40.6 (Din), SW44.4 (Dout)
unnamed: SW41.6 (Din), SW45.4 (Dout)
unnamed: SW42.6 (Din), SW46.4 (Dout)
unnamed: SW43.6 (Din), SW47.4 (Dout)
unnamed: SW44.6 (Din), SW49.4 (Dout)
unnamed: SW45.6 (Din), SW50.4 (Dout)
unnamed: SW46.6 (Din), SW51.4 (Dout)
unnamed: SW47.6 (Din), SW52.4 (Dout)
unnamed: SW49.6 (Din), SW54.4 (Dout)
unnamed: SW50.6 (Din), SW55.4 (Dout)
unnamed: SW51.6 (Din), SW61.4 (Dout)
unnamed: SW9.6 (LED1_Dout), SW52.6 (Din)
unnamed: SW54.6 (Din), SW59.4 (Dout)
unnamed: SW55.6 (Din), SW60.4 (Dout)
unnamed: SW59.6 (Din), SW63.4 (Dout)
unnamed: SW60.6 (Din), SW64.4 (Dout)
unnamed: SW61.6 (Din), SW65.4 (Dout)
unnamed: SW9.12 (LED2_Din), SW66.4 (Dout)
unnamed: U5.6 (LED1In), U5.10 (LED2Out)
unnamed: U5.12 (LED2In), U5.16 (LED3Out)
unnamed: U5.18 (LED3In), U5.22 (LED4Out)
unnamed: U5.24 (LED4In), U5.56 (LED5Out)
unnamed: U5.28 (LED6Out), U5.58 (LED5In)
unnamed: U5.30 (LED6In), U5.34 (LED7Out)
unnamed: U5.36 (LED7In), U5.40 (LED8Out)
unnamed: U5.42 (LED8In), U5.46 (LED9Out)
unnamed: U5.48 (LED9In), U5.52 (LED10Out)

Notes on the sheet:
ROWS = 5 COLS = 14 ROW 0 length = 14 Til 1 2 3 4 5 6 7 8 9 0 - = Backspace ROW 1 length = 14 Tab q w e r t y u i o p [ ] \ ROW 2 lenght = 13 Caps a s d f g h j k l ; ' ## Enter ROW 3 length = 12 LShift ## z x c v b n m , . / RShift ## ROW 4 length = 8 RCtrl RGUI RAlt ## ## ## Space ## ## ## RAlt RG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
Right Shift & Up
